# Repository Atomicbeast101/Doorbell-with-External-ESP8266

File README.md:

# Smart Doorbell

A KiCad-designed smart doorbell PCB that provides the capability to use the existing doorbell transformer to power the board (via a buck converter), utilize the existing doorbell button wiring, and control the doorbell chime. The idea is to leverage the existing equipment and make it smarter by enabling it to detect doorbell presses and send notifications to Home Assistant while still triggering the doorbell chime.

This design has gone through its second revision to achieve a working version. The third revision was done to improve the wiring layout, otherwise the schematic design is the same.

* **v1.0** - Wrong MOSFET chip, resulting in ESP8266 not having the ability to control the relay to trigger the doorbell chime.
* **v1.1** - Working version
* **v1.2** - Changed layout to simplify wire management between the buck converter and the doorbell hardware (transformer, chime & doorbell). This version was ordered through PCBWay (see below for more details).

## PCBWay Sponsorship

PCBWay reached out to me in October 2024 to sponsor the manufacturing of the **v1.2** revision.

They have a pretty cool plugin for KiCad that generates the manufacturing files and sends them directly to PCBWay's ordering page. All I had to do was review the order options, modify any as needed, and add it to my cart. The main difference from JLCPCB is that I didn't have to identify the part numbers in the schematic file; they did it for me, which is nice.

However, it would be beneficial to have the option to specify which part numbers should be identified, so they would only need to reach out to me for confirmation on the quote rather than asking me for part numbers on the non-assembled parts.

After a few weeks, the PCBs were shipped to me. I am quite satisfied with their manufacturing quality. One nice feature is that they provide one PCB without any assembled parts, along with five that have the components soldered on. This could be useful for those who want to see how it looks without the parts in the way for troubleshooting purposes. I was able to get other parts soldered on without any issues.

You can check out their site for more details or to place an order: https://www.pcbway.com/.

## Specifications

* Buck converter is required to power this board via 16VAC doorbell transformer ([Amazon Link](https://www.amazon.com/UMLIFE-Converter-2-5-35V-Regulator-Adjustable/dp/B094ZTG5S8)). **It needs to be adjusted to output 5v DC before connecting to this smart doorbell device.**
* 5v DC (output from DC for doorbell button) is used to power the doorbell instead of 16VAC from the transformer
* Uses ESPHome to handle the doorbell action like a traditional one, communicate updates to Home Assistant and to control the ESPHome-based smart bulbs to flash.
    * This is to allow the doorbell to function if Home Assistant is down.
    * The ESPHome YAML config can be found under `ESPHome/` folder (WIP as of 10/2/2024).

## Doorbell Wire Diagram

Here's a diagram of how this smart doorbell interacts with a typical home's doorbell system with standard 16VAC transformer.

## Viewing Schematic & PCB Design

The designs can be seen using Kicanvas tool [here](https://kicanvas.org/?github=https%3A%2F%2Fgithub.com%2FAtomicbeast101%2Fsmart-doorbell) (this tool is still in alpha stage as of September 2024).

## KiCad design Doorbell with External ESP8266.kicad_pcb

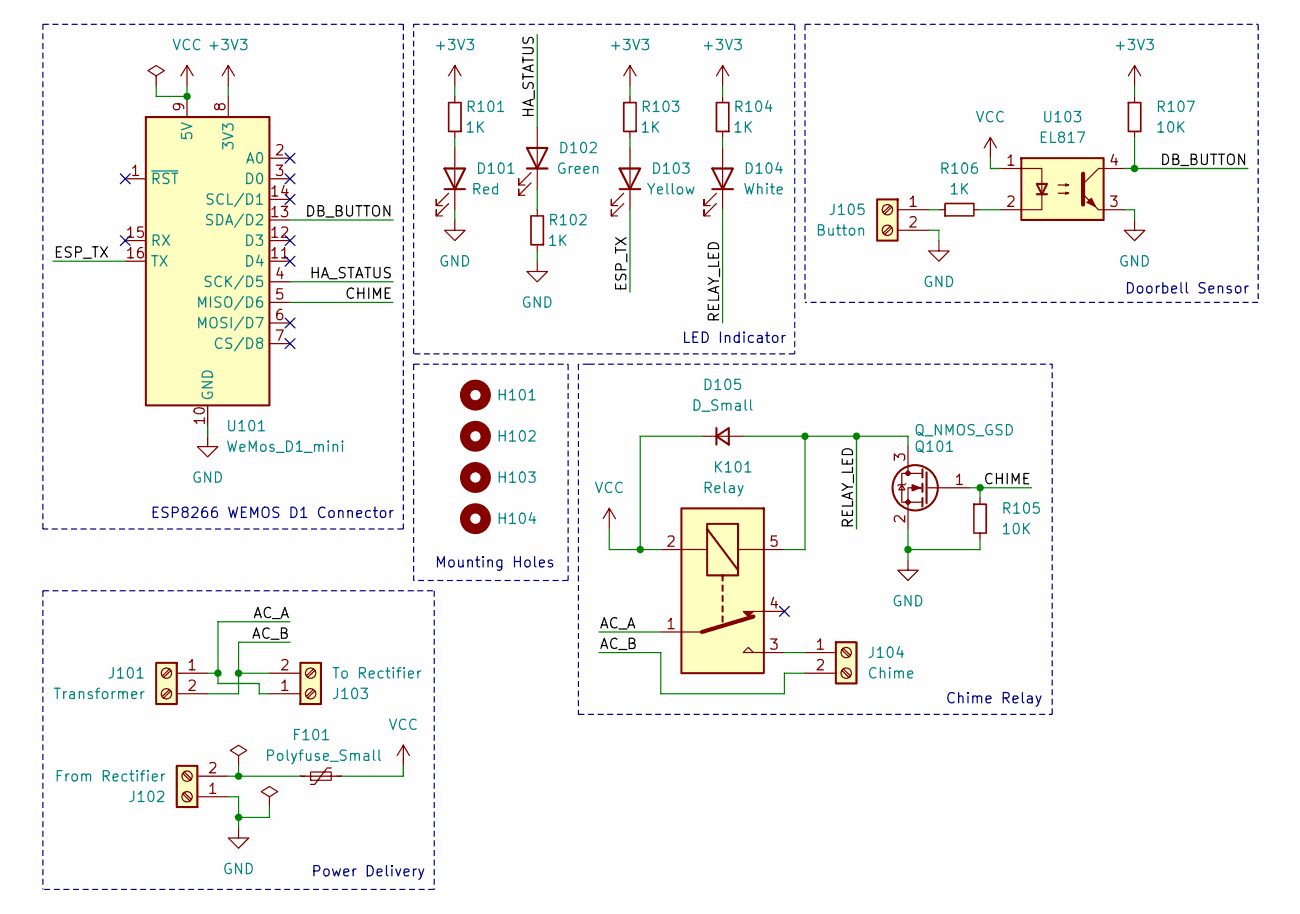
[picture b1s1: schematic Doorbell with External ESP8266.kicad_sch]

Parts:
D101: Red; LED_0805_2012Metric; LCSC C84256
D102: Green; LED_0805_2012Metric; LCSC C2297
D103: Yellow; LED_0805_2012Metric; LCSC C2296
D104: White; LED_0805_2012Metric; LCSC C34499
D105: D_Small; D_SMA; LCSC C8678
F101: Polyfuse_Small; Fuse_1812_4532Metric; LCSC C12559
H101, H102, H103, H104: MountingHole; MountingHole_3mm
J101: Transformer; TerminalBlock_Phoenix_MKDS-1,5-2_1x02_P5.00mm_Horizontal
J102: From Rectifier; TerminalBlock_Phoenix_MKDS-1,5-2_1x02_P5.00mm_Horizontal
J103: To Rectifier; TerminalBlock_Phoenix_MKDS-1,5-2_1x02_P5.00mm_Horizontal
J104: Chime; TerminalBlock_Phoenix_MKDS-1,5-2_1x02_P5.00mm_Horizontal
J105: Button; TerminalBlock_Phoenix_MKDS-1,5-2_1x02_P5.00mm_Horizontal
K101: Relay; Relay_SPDT_SANYOU_SRD_Series_Form_C
Q101: Q_NMOS_GSD; SOT-23; LCSC C8545
R101, R102, R103, R104, R106: 1K; R_0603_1608Metric; LCSC C21190
R105, R107: 10K; R_0603_1608Metric; LCSC C25804
U101: WeMos_D1_mini; WEMOS_D1_mini_light
U103: EL817; EL817S1(C)(TU)-F; LCSC C106900

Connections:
+3V3: R101.2, R103.2, R104.2, R107.1, U101.8 (3V3)
/AC_A: J101.1, J103.1, K101.1
/AC_B: J101.2, J103.2, J104.2
/CHIME: Q101.1 (G), R105.1, U101.5 (MISO/D6)
/DB_BUTTON: R107.2, U101.13 (SDA/D2), U103.4
/ESP_TX: D103.1 (K), U101.16 (TX)
/HA_STATUS: D102.2 (A), U101.4 (SCK/D5)
/RELAY_LED: D104.1 (K), D105.2 (A), K101.5, Q101.3 (D)
GND: D101.1 (K), J102.1, J105.2, Q101.2 (S), R102.1, R105.2, U101.10 (GND), U103.3
unnamed: D101.2 (A), R101.1
unnamed: D102.1 (K), R102.2
unnamed: D103.2 (A), R103.1
unnamed: D104.2 (A), R104.1
unnamed: F101.1, J102.2
unnamed: J104.1, K101.3
unnamed: J105.1, R106.1
unnamed: R106.2, U103.2
VCC: D105.1 (K), F101.2, K101.2, U101.9 (5V), U103.1

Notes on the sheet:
LED Indicator
Chime Relay
ESP8266 WEMOS D1 Connector
Doorbell Sensor
Mounting Holes
Power Delivery

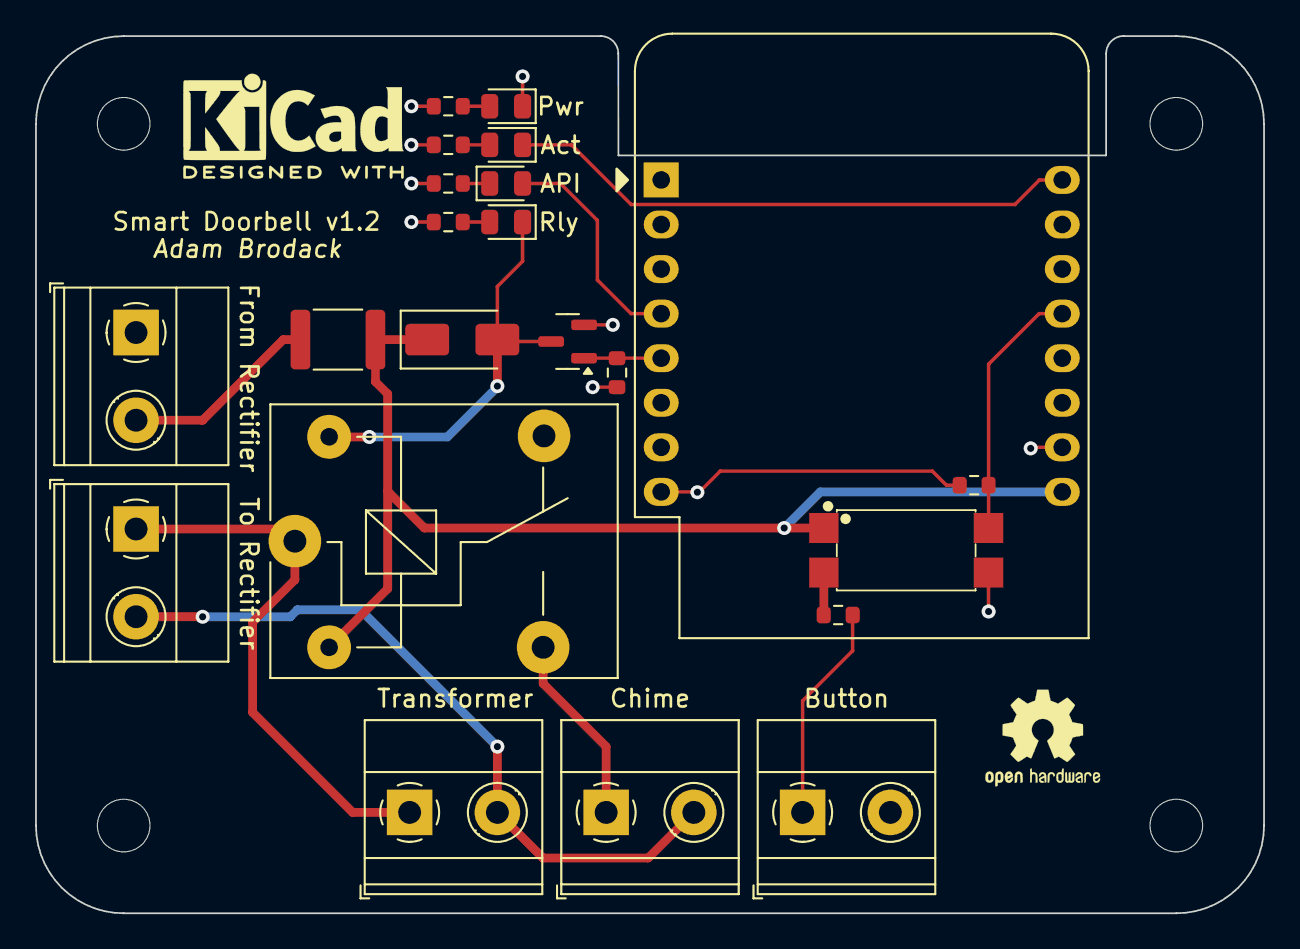
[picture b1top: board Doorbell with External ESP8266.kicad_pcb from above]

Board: 4 copper layers, 70.0 x 50.0 mm, 26 parts (0 on the bottom side), 18 nets.

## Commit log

2024-06-20 Created schematic & PCB
2024-06-22 Removed CHIME & improved wiring
2024-06-30 Added ability to control chime from ESP8266
2024-07-11 Updated schematic & PCB
2024-07-13 Improved the location for the LEDs & increased trace size for power from rectifier
2024-07-13 Fix any errors after DRC validation
2024-07-13 Generated JLCPCB files for order
2024-07-13 Added JLCPCB silkscreen object for order #
2024-07-30 Moved power to different level & made JLCPCB order
2024-08-17 schematic fix
2024-08-18 Fixed MOSFET for relay & moved some parts around to make it better
2024-08-25 Added README
2024-08-25 Added details around ESPHome
2024-08-29 Updated status of 2nd revision
2024-08-31 Updated to include comments on size of PCB board
2024-08-31 Removed jlcpcb files
2024-10-01 Added more technical docs for v1.2 revision
2024-10-01 Updated more content in PCBWay Sponsorship section
2024-10-02 Updated PCBWay content from company's feedback
2024-10-03 Fixed grammar
2024-10-03 Added note for empty ESPHome folder
2024-10-11 Added 3D-model of the PCB board for making case
2024-10-11 Added buck converter model
